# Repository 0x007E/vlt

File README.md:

# `VLT` - Data Vault

The `VLT` is a board with an [RNG90](#additional-information) and a `TRNG` based on a digital circuit. It is possible to generate random numbers and print them over `UART`. The board itself is driven with `5V` over a `USBC` connector. The board itself can be programmed over `USB` and `avr-dude` (`serialupdi`). To programm the board over `USB` (`UART`) it is necessary to enable the `UPDI` programming function (over the onboard dip-switches). 

| Experience  | Level                                                                               |
|:------------|:-----------------------------------------------------------------------------------:|
| Soldering   |  |
| Mechanical  |     |

# Downloads

| Type      | File                                                                                                                                                 | Description     |
|:---------:|:----------------------------------------------------------------------------------------------------------------------------------------------------:|:----------------|
| Schematic | [pdf](https://github.com/0x007E/vlt/releases/latest/download/schematic.pdf) / [cadlab](https://cadlab.io/project/29805/main/files)                   | Schematic files |
| Board     | [pdf](https://github.com/0x007E/vlt/releases/latest/download/pcb.pdf) / [cadlab](https://cadlab.io/project/29805/main/files)                         | Board file      |
| Drill     | [pdf](https://github.com/0x007E/vlt/releases/latest/download/drill.pdf)                                                                              | Drill file      |
| BoM | [xlsx](https://github.com/0x007E/vlt/releases/latest/download/bom.xlsx) / [html](https://github.com/0x007E/vlt/releases/latest/download/ibom.html)          | Bill of Material as Excel/interactive HTML |
| PCB    | [zip](https://github.com/0x007E/vlt/releases/latest/download/kicad.zip) / [tar](https://github.com/0x007E/vlt/releases/latest/download/kicad.tar.gz)    | KiCAD/Gerber/BoM/Drill files       |
| Mechanical | [zip](https://github.com/0x007E/vlt/releases/latest/download/freecad.zip) / [tar](https://github.com/0x007E/vlt/releases/latest/download/freecad.tar.gz) | FreeCAD/Housing and PCB (STEP/STL) files     |

# Hardware

The pcb is created with `KiCAD`, the housing with `FreeCAD`. All files are built with `github actions` so that they are ready for a production environment.

## PCB

The circuit board is populated on both sides (Top, Bottom). The best way for soldering the `SMD` components is within a vapor phase soldering system and for the `THT` components with a standard soldering system.

### Top Layer

### Bottom Layer

## Mechanical

The housing has a tolerance of `0.2mm` on each side of the case. So the pcb should fit perfectly in the housing. The tolerance can be modified with `FreeCAD` in the `Parameter` Spreadsheet.

### Assembled

### Exploded

# Additional Information

| Type       | Link               | Description              |
|:----------:|:------------------:|:-------------------------|
| FT232RL    | [pdf](https://ftdichip.com/wp-content/uploads/2020/08/DS_FT232R.pdf) | USB Full Speed to Serial UART IC, Includes Oscillator and EEPROM |
| RNG90      | [pdf](https://ww1.microchip.com/downloads/aemDocuments/documents/SCBU/ProductDocuments/DataSheets/RNG90-CryptoAuthentication-Data-Sheet-DS40002499.pdf) | RNG90 CryptoAuthentication |

---

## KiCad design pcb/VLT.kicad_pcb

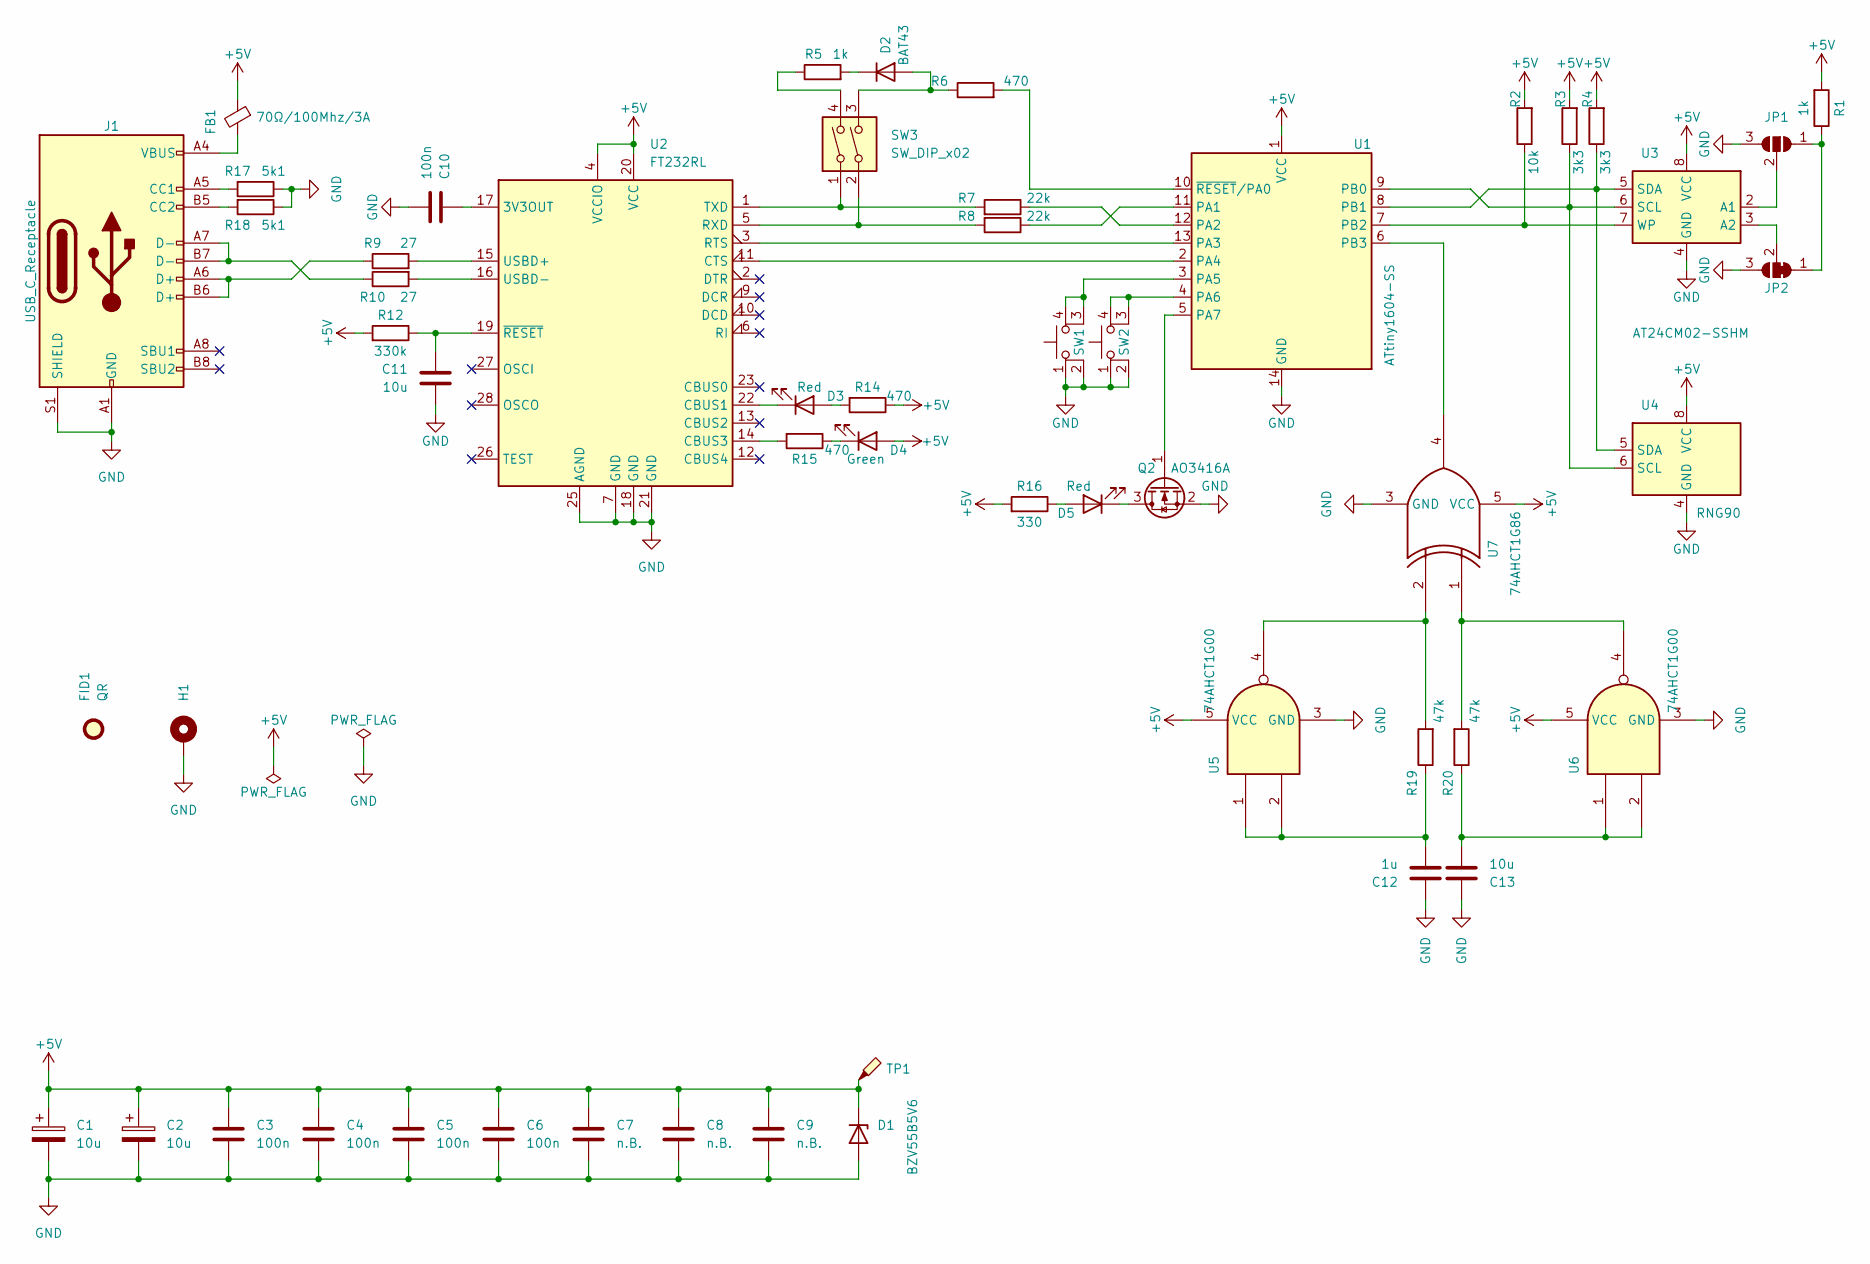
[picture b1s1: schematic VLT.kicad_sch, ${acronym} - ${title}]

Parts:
C1, C2: 10u; CP_EIA-3528-21_Kemet-B
C3, C4, C5, C6, C10: 100n; C_1206_3216Metric
C7, C8, C9: n.B.; C_1206_3216Metric
C11, C13: 10u; C_1206_3216Metric
C12: 1u; C_1206_3216Metric
D1: BZV55B5V6; D_MiniMELF
D2: BAT43; D_MiniMELF
D3, D5: Red; LED_1206_3216Metric
D4: Green; LED_1206_3216Metric
FB1: 70Ω/100Mhz/3A; L_1206_3216Metric
FID1: QR; QR_0x007e_very_small
H1: MountingHole_Pad; MountingHole_3.2mm_M3_DIN965_Pad
J1: USB_C_Receptacle; USB_C_Receptacle_GCT_USB4110
JP1: SolderJumper_3_Open; SolderJumper-3_P1.3mm_Open_RoundedPad1.0x1.5mm
JP2: SolderJumper_3_Bridged12; SolderJumper-3_P1.3mm_Bridged12_RoundedPad1.0x1.5mm
Q2: AO3416A; SOT-23
R1, R5: 1k; R_1206_3216Metric
R2: 10k; R_1206_3216Metric
R3, R4: 3k3; R_1206_3216Metric
R6, R14, R15: 470; R_1206_3216Metric
R7, R8: 22k; R_1206_3216Metric
R9, R10: 27; R_1206_3216Metric
R12: 330k; R_1206_3216Metric
R16: 330; R_1206_3216Metric
R17, R18: 5k1; R_1206_3216Metric
R19, R20: 47k; R_1206_3216Metric
SW1, SW2: SW_MEC_5E; SW_PTS530_GK055_SMTR_LFS
SW3: SW_DIP_x02; SW_DIP_SPSTx02_Slide_6.7x6.64mm_W8.61mm_P2.54mm_LowProfile
TP1: TestPoint_Probe; TestPoint_Pad_D1.0mm
U1: ATtiny1604-SS; SOIC-14_3.9x8.7mm_P1.27mm
U2: FT232RL; SSOP-28_5.3x10.2mm_P0.65mm
U3: AT24CM02-SSHM; SOIC-8_3.9x4.9mm_P1.27mm
U4: RNG90; SOIC-8_3.9x4.9mm_P1.27mm
U5, U6: 74AHCT1G00; SOT-23-5
U7: 74AHCT1G86; SOT-23-5

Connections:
+5V: C1.1, C2.1, C3.1, C4.1, C5.1, C6.1, C7.1, C8.1, C9.1, D1.1 (K), D4.2 (A), FB1.1, R1.2, R2.2, R3.2, R4.2, R12.2, R14.1, R16.2, TP1.1, U1.1 (VCC), U2.4 (VCCIO), U2.20 (VCC), U3.8 (VCC), U4.8 (VCC), U5.5 (VCC), U6.5 (VCC), U7.5 (VCC)
GND: C1.2, C2.2, C3.2, C4.2, C5.2, C6.2, C7.2, C8.2, C9.2, C10.1, C11.2, C12.1, C13.1, D1.2 (A), H1.1, J1.A1 (GND), J1.A12 (GND), J1.B1 (GND), J1.B12 (GND), J1.S1 (SHIELD), JP1.3 (B), JP2.3 (B), Q2.2 (S), R17.1, R18.1, SW1.1, SW1.2, SW2.1, SW2.2, U1.14 (GND), U2.7 (GND), U2.18 (GND), U2.21 (GND), U2.25 (AGND), U3.4 (GND), U4.4 (GND), U5.3 (GND), U6.3 (GND), U7.3 (GND)
unnamed: C12.2, R19.1, U5.1, U5.2
unnamed: C13.2, R20.1, U6.1, U6.2
unnamed: D2.2 (A), R6.1, SW3.3
unnamed: D2.1 (K), R5.2
unnamed: D3.2 (A), R14.2
unnamed: D3.1 (K), U2.22 (CBUS1)
unnamed: D4.1 (K), R15.1
unnamed: D5.2 (A), R16.1
unnamed: D5.1 (K), Q2.3 (D)
unnamed: FB1.2, J1.A4 (VBUS), J1.A9 (VBUS), J1.B4 (VBUS), J1.B9 (VBUS)
unnamed: J1.A5 (CC1), R17.2
unnamed: J1.B5 (CC2), R18.2
unnamed: J1.A6 (D+), J1.B6 (D+), R9.1
unnamed: J1.A7 (D-), J1.B7 (D-), R10.1
unnamed: JP1.1 (A), JP2.1 (A), R1.1
unnamed: JP1.2 (C), U3.2 (A1)
unnamed: JP2.2 (C), U3.3 (A2)
unnamed: Q2.1 (G), U1.5 (PA7)
unnamed: R5.1, SW3.4
unnamed: R19.2, U5.4, U7.2
unnamed: R20.2, U6.4, U7.1
unnamed: SW1.3 (K), SW1.4 (A), U1.3 (PA5)
unnamed: SW2.3 (K), SW2.4 (A), U1.4 (PA6)
unnamed: R8.1, U1.11 (PA1)
unnamed: R7.1, U1.12 (PA2)
unnamed: U1.13 (PA3), U2.3 (RTS)
unnamed: U1.2 (PA4), U2.11 (CTS)
unnamed: R3.1, U1.9 (PB0), U3.6 (SCL), U4.6 (SCL)
unnamed: R4.1, U1.8 (PB1), U3.5 (SDA), U4.5 (SDA)
unnamed: R2.1, U1.7 (PB2), U3.7 (WP)
unnamed: U1.6 (PB3), U7.4
unnamed: R6.2, U1.10 (~RESET/PA0)
unnamed: C10.2, U2.17 (3V3OUT)
unnamed: R15.2, U2.14 (CBUS3)
unnamed: R8.2, SW3.2, U2.5 (RXD)
unnamed: R7.2, SW3.1, U2.1 (TXD)
unnamed: R9.2, U2.15 (USBD+)
unnamed: R10.2, U2.16 (USBD-)
unnamed: C11.1, R12.1, U2.19 (~RESET)

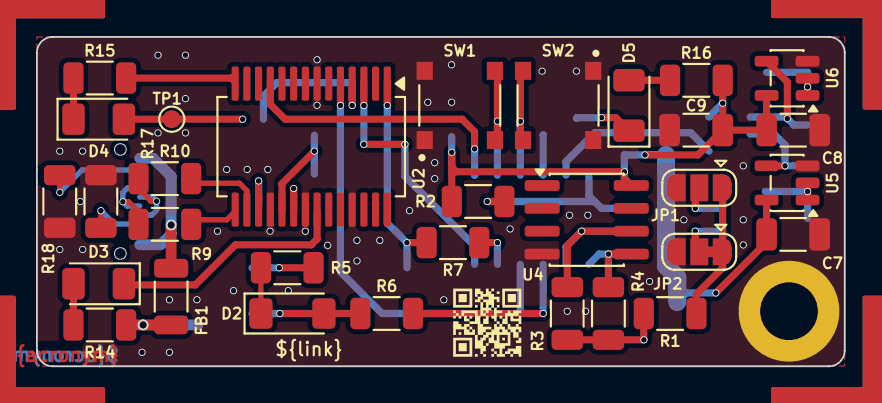
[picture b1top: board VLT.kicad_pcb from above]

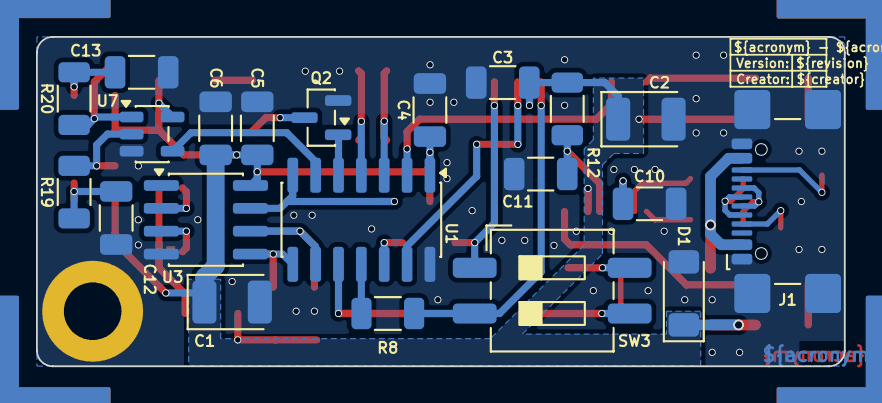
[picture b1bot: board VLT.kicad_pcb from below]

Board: 2 copper layers, 44.9 x 18.3 mm, 54 parts (21 on the bottom side), 41 nets.

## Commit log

2025-12-17 Add pcb layout
2025-12-17 Add mechanical parts
2026-01-03 Change partlist vendors
2026-01-22 Adapt values for rng
2026-01-22 Add test firmware
2026-01-24 Disable uart rxc echo
2026-01-24 Add rtc library
2026-01-24 Extend wait functions
2026-01-24 Remove delay and add systick functions
2026-01-24 Modified systick functions
2026-01-24 Add console library
2026-01-26 Make hal adjustable
2026-01-26 Add preprocessor macros to utils
2026-04-03 Add submodules to library
2026-04-03 Add global defines information
2026-04-09 Optimize fabrication layer
2026-06-16 Update to KiCAD 9
2026-06-16 Rename/Add/Remove bom fields
2026-06-16 Add README.md
2026-06-16 Optimize assembly explosion
2026-06-16 Add build pipeline
2026-06-16 Add release pipeline
2026-06-17 Add adapted pcb layout
2026-06-22 Adapt output filenames
2026-06-22 Add missing values in bom
2026-06-22 Adapt config and update action versions
2026-06-22 Remove invalid layer
2026-06-22 Fix freecad path issue

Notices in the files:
README.md:
License CC By-NC-SA
parts and their libraries:
license: CC BY-NC-SA 4.0
